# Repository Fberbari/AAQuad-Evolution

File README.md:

# AAQuad-Evolution
---

The AAQuad-Evolution is a flight computer I've designed to control a quadcopter. The computer takes care of continued stabilization in flight while leaving the pilot free to command roll, pitch, and yaw angles as well as altitude. The project is made up of a custom PCB, all the bare-metal C code that runs on the Atmega328pb processor and Matlab simulations used to design and tune the PID algorithms. This is very much a bare bones flight computer that is in no way as feature rich as BetaFlight or any of the other famous FOS flight controllers. Its advantage lies in its simplicity. Anyone with some understanding of the dynamics of flight, calculus, and circuitry could begin to understand the project without being faced with a mountain of complexity and no idea where to start. In the end, the AAQuad-Evolution continues to satisfy my curiosity for flight and increase my understanding of embedded systems all the while providing me with a creative outlet to try out all kinds of cool things.

## Flying the Quad
---

The commands are as such:

* Increasing/decreasing the throttle stick corresponds to an increase/decrease in the target altitude.
* Increasing/decreasing the rudder stick corresponds to an increase/decrease in the target azimuth (relative to the starting azimuth).
* Increasing/decreasing the aileron stick corresponds to an increase/decrease in the target bank angle.
* Increasing/decreasing the elevator stick corresponds to an increase/decrease in the target pitch angle.

The ranges for all the mentioned targets are defined in src/Pid.h.

## Calibrating the Quad
---

1. Before plugging in the battery, turn the transmitter on and put the throttle stick to full power.
2. Plug in the battery.
	* A solid green led will turn on, indicating calibration mode has been successfully entered.
3. Position the Quad on a level surface and make sure it is completely still.
4. Put the throttle stick to 0.
	* The led will turn off, indicating calibration has begun.
5. Once the led turns on again, the Quad has been successfully calibrated and is ready to be flown.

### Some in flight images

### Some close ups

## What's going on ?
---

So you want to understand how the AAQuad flies ? Great! Here is a high level explanation of what's going on.

Everything starts in main.c, which you'll find in the root directory of the project. If you go through that file, you'll find it's incredibly simple in principle. Here, we begin with a short delay to ensure all electrical systems have stabilized after power up. Next, we execute a calibration and finally, we call the controller state machine inside an infinite loop (this is where the magic happens).

Now, let's head into the src directory. Apart from main.c, this is where all the the source and header files are stored. Take a look at the state machine in Controller.c (the switch case statement inside the Controller_DoYourThingAndFlyTheQuadITrustYou function). The switch statement is organized in the order that the states get executed. Here's what's going on:

1. GetPilotInstructions: We check to see whether there are any new instructions from the receiver. If you take a look inside the PilotInstructions module, you'll see that the pwm signals sent from the ESC are read asynchronously via external and pin change interrupts. Those instructions get translated into percentages for commanded roll, pitch, yaw and altitude. If they are ready when PilotInstructions_ComputePilotResult is called, we pick them up. Otherwise, we just move on and pick them up the next time.

2. GetImuData: We collect the accelerometer, gyroscope and magnetometer data from the inertial measurement unit. This is also an interrupt based exchanged so when we call Imu_GetResult, we are just checking if the data is ready and picking it up if it is.

3. GetAltitude: We collect data from the ultrasonic distance sensor. Once again, it is an interrupt based exchange, so we are just checking and picking data up if it is ready.

4. TriggerNewMeasurements: Now that we've collected all the data of interest, we need to instruct the sensors to collect more data for us. This way, when the time comes once again to ask for it, it will be ready. For the IMU, this triggers an interrupt based SPI exchange that reads the registers that contain the relevant data. For the ultrasonic distance sensor, this sends the digital pulse instructing it to collect a new measurement.

5. FuseMeasurements: While the sensors do their thing, we begin to crunch the math. In this state, we fuse gyroscope and accelerometer data together using a Mahony filter. This filter returns the estimated orientation of the quad encoded in a quaternion.

6. ConvertToEuler: Since quaternions are very non linear and thus hard to use in a linear controller, we convert them into Euler angles. These are the familiar roll, pitch and yaw angles. At the same time, we also compute the derivatives of the Euler angles (representative of the angular velocity of the quad in every axis). This is for future use in the controller. It is done this way because computing a derivative from the change in measured angular positions leaves us very susceptible to noise. Since we have a gyroscope and measure the derivatives directly, we can use those values and avoid this problem.

7. ComputePid: Now that we know what the pilot wants and what the quad is doing, we can compute what we need the motors to do to achieve the pilot's intentions. This is done via multiple PID (proportional, integral, derivative) algorithms. This module also takes care of figuring out the takeoff sequence of the quad. What we get from it is an array of 4 floats that correspond to percentages of full power that need to be delivered to each motor to achieve the desired intentions.

8. SendToPwm: Once we know what we want the motors to do, we need to communicate that to them. To do so, we begin an interrupt based I2C exchange with a chip responsible for sending out PWM to the ESC.

9. WaitForTimer: Last, to keep things synchronous, we sit in this state until a timer says some set time has passed. Once that is the case, we go back to the GetPilotInstructions state and the cycle begins anew.

10. Failed: This state should never be reached in normal flight but exists in case a catastrophic failure needs to be handled. In the case that something goes horribly wrong in one of the modules (for example communication gets cut with one of our chips), we go to this state and the PWM output to the ESC gets immediately shutdown, causing the motors to stop spinning.

## Building it for yourself
---

A word of caution. This project was not designed to be reproduced, so it is fairly difficult to do so. That being said, if anyone does want to construct the PCB and tune then upload the software, here is what they would need to do:

### Prereq Hardware

* [Avr-Ice Jtag programmer](https://www.digikey.ca/en/product-highlight/a/atmel/atmel-ice-programmer-debugger?utm_adgroup=&utm_source=google&utm_medium=cpc&utm_campaign=Dynamic%20Search_EN_RLSA&utm_term=&productid=&gclid=Cj0KCQjw-r71BRDuARIsAB7i_QPVjor9MwRzLKq1k-X_j-4Pasl5VIqnCOX7berqcM59qXUvdlT64RQaAkUuEALw_wcB)
* A 4 channel ESC with 5V BEC that can handle 200 Hz PWM refresh rates
* A minimum 4 channel receiver that communicates over PWM
* Your favorite quadcopter frame, motors, and battery
* A transmitter capable of communicating with your esc of choice

### Prereq Software

* Atmel studio 7+
* Kicad 5+ (Optional, as the gerbers are already in the repo)
* Simulink 2019+, equipped with the aerospace blockset

### Building the PCB

Full gerber files and a BOM are present in the PCB/KicadFiles directory.
The only sensor not present in the BOM is the [ultrasonic distance sensor](https://www.sparkfun.com/products/15569).
You will also need to purchase the appropriate wires to connect the ESC, receiver, and ultrasonic sensor to the PCB.

### Adjusting the PID gains

If you know the mass, inertia tensor, and relationship between throttle percentage, force and torque of your quadcopter, you can adjust the appropriate blocks in the Simulink model and tune the PID gains. You can insert those gains into src/Pid.c.

### Compiling and uploading the software

Once the pcb is built, power it by connecting the ESC to the battery and plug in the Jtag programmer to the appropriate pins. To open the project in Atmel studio, open the project file present in /build. Then, click the compile button and the run button.

## License

This project is under the MIT license.

## Acknowledgements

* SOH Madgwick, whose implementation of the Mahony filter is used in this project.
* A shoutout to Anny Wang, who said: "Hey, wouldn't it be cool to build a quadcopter ?" back in 2018, which is how this project began :p.

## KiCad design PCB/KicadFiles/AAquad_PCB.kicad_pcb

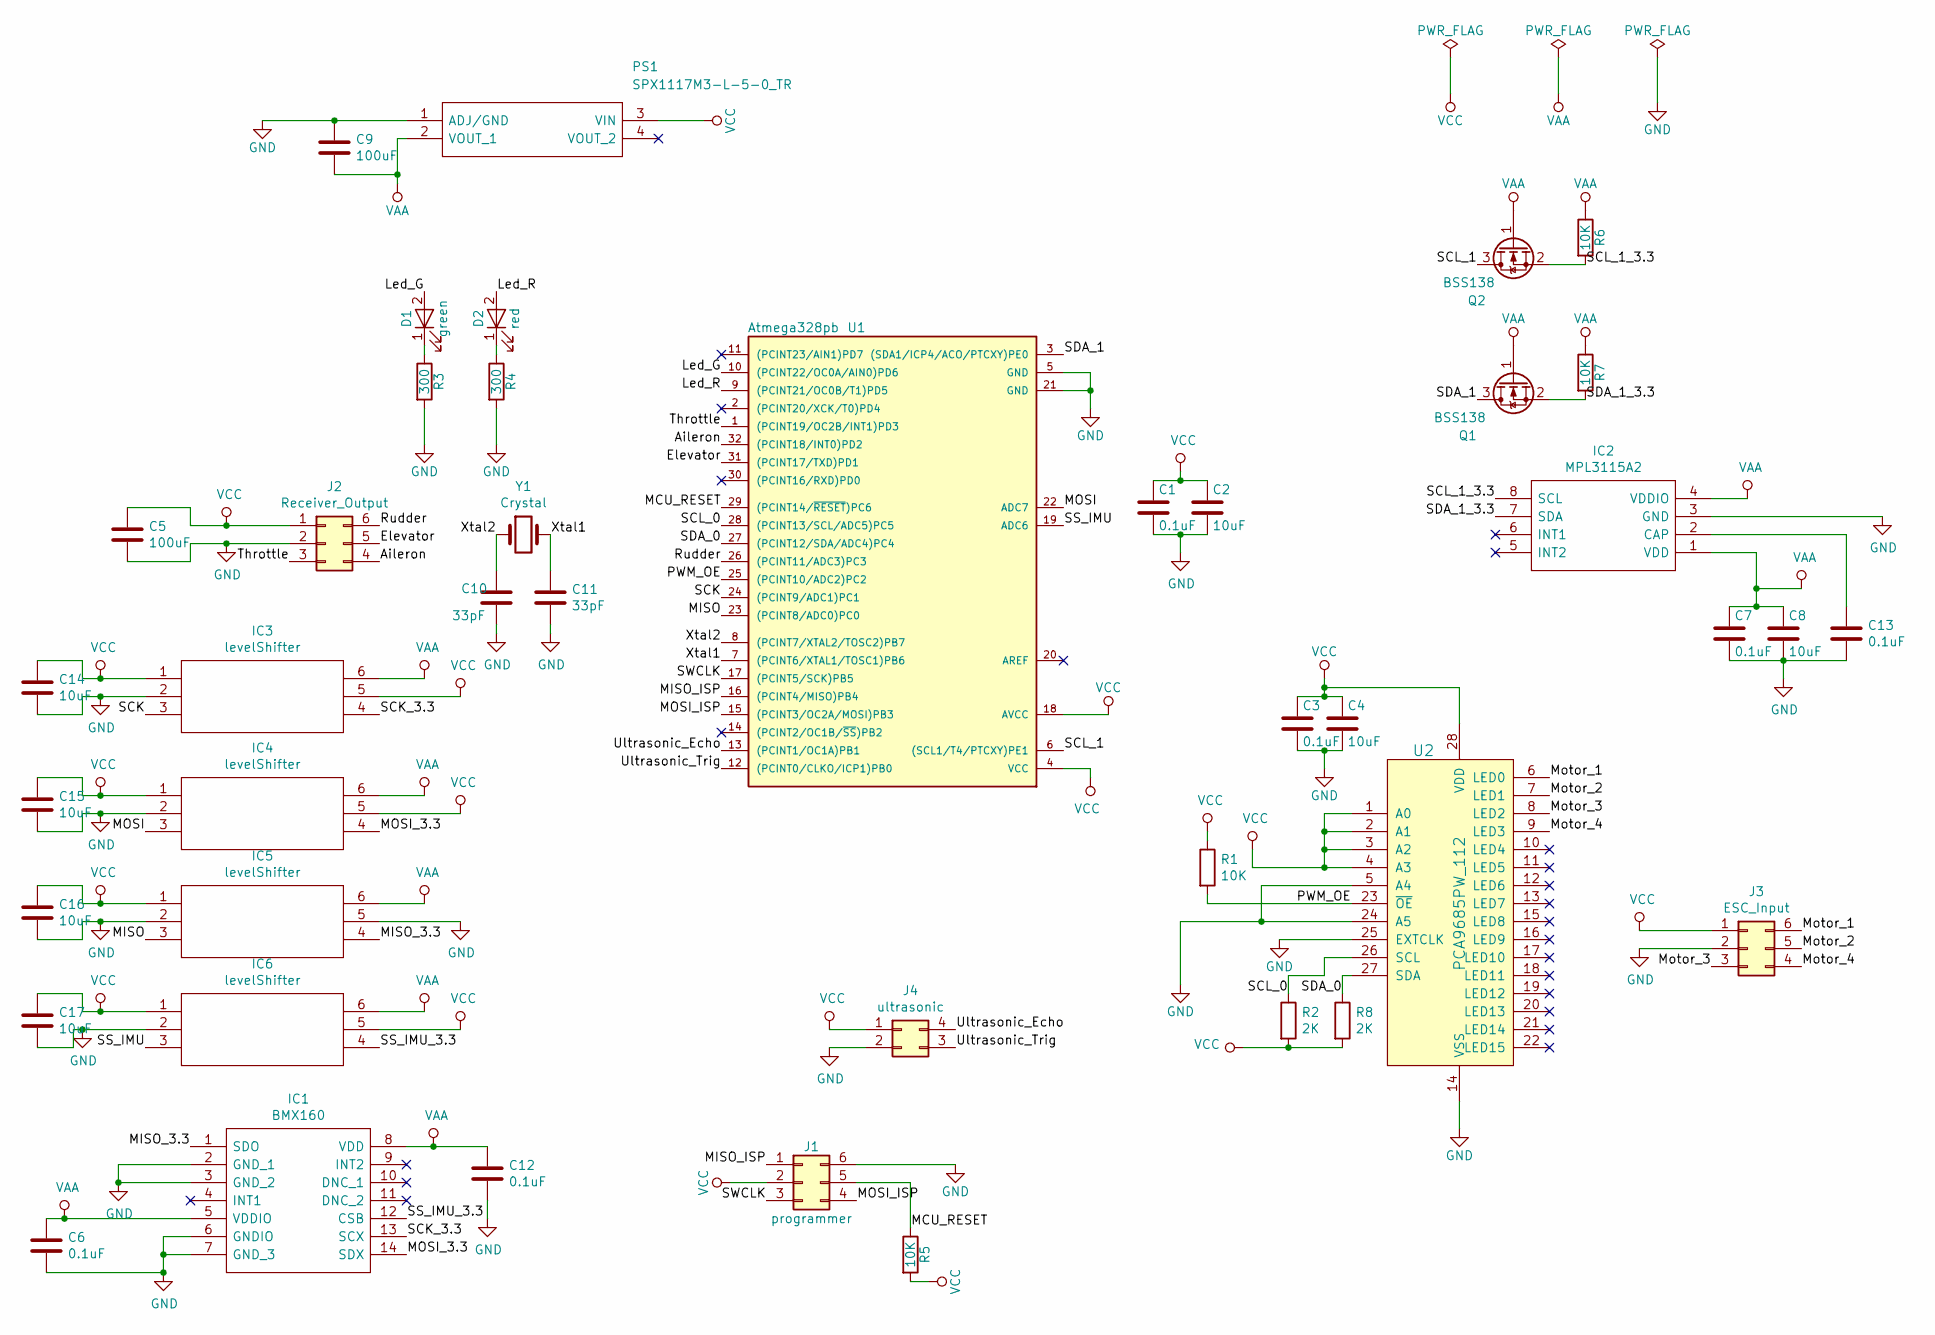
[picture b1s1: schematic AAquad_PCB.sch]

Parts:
C1, C3, C6, C7, C12, C13: 0.1uF; C_0805
C2, C4, C8: 10uF; C_0805
C5, C9: 100uF; C_1206_3216Metric
C10, C11: 33pF; C_0402_1005Metric
C14, C15, C16, C17: 10uF; C_0805_2012Metric
D1: green; LED_0805_HandSoldering
D2: red; LED_0805_HandSoldering
IC1: BMX160; bmx160; Manufacturer_Part_Number BMX160; Mouser Part Number 262-BMX160
IC2: MPL3115A2; Manufacturer_Part_Number MPL3115A2
IC3, IC4, IC5, IC6: levelShifter; 74LVC1T45GW_125; Mouser Part Number 771-74LVC1T45GW125
J1: programmer; PinHeader_2x03_P2.54mm_Vertical
J2: Receiver_Output; PinHeader_2x03_P2.54mm_Vertical
J3: ESC_Input; PinHeader_2x03_P2.54mm_Vertical
J4: ultrasonic; PinHeader_2x02_P2.54mm_Vertical
PS1: SPX1117M3-L-5-0_TR; SOT230P700X170-4N; Manufacturer_Part_Number SPX1117M3-L-5-0/TR
Q1, Q2: BSS138; SOT-23
R1, R5, R6, R7: 10K; R_0805_2012Metric
R2, R8: 2K; R_0805_2012Metric
R3, R4: 300; R_0805_2012Metric
U1: Atmega328pb; ATMEGA328PB-ANR
U2: PCA9685PW_112; TSSOP-28_W4.40mm; MPN PCA9685PW,112; Digi-Key_PN 568-8366-5-ND
Y1: Crystal; Crystal_SMD_7050-2pin_7.0x5.0mm

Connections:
/Aileron: J2.4, U1.32 ((PCINT18/INT0)PD2)
/Elevator: J2.5, U1.31 ((PCINT17/TXD)PD1)
/Led_G: D1.2 (A), U1.10 ((PCINT22/OC0A/AIN0)PD6)
/Led_R: D2.2 (A), U1.9 ((PCINT21/OC0B/T1)PD5)
/MCU_RESET: J1.5, R5.1, U1.29 ((PCINT14/~RESET~)PC6)
/MISO: IC5.3, U1.23 ((PCINT8/ADC0)PC0)
/MISO_3.3: IC1.1 (SDO), IC5.4
/MISO_ISP: J1.1, U1.16 ((PCINT4/MISO)PB4)
/MOSI: IC4.3, U1.22 (ADC7)
/MOSI_3.3: IC1.14 (SDX), IC4.4
/MOSI_ISP: J1.4, U1.15 ((PCINT3/OC2A/MOSI)PB3)
/Motor_1: J3.6, U2.6 (LED0)
/Motor_2: J3.5, U2.7 (LED1)
/Motor_3: J3.3, U2.8 (LED2)
/Motor_4: J3.4, U2.9 (LED3)
/PWM_OE: R1.2, U1.25 ((PCINT10/ADC2)PC2), U2.23 (~OE)
/Rudder: J2.6, U1.26 ((PCINT11/ADC3)PC3)
/SCK: IC3.3, U1.24 ((PCINT9/ADC1)PC1)
/SCK_3.3: IC1.13 (SCX), IC3.4
/SCL_0: R2.1, U1.28 ((PCINT13/SCL/ADC5)PC5), U2.26 (SCL)
/SCL_1: Q2.3 (D), U1.6 ((SCL1/T4/PTCXY)PE1)
/SCL_1_3.3: IC2.8 (SCL), Q2.2 (S), R6.2
/SDA_0: R8.1, U1.27 ((PCINT12/SDA/ADC4)PC4), U2.27 (SDA)
/SDA_1: Q1.3 (D), U1.3 ((SDA1/ICP4/ACO/PTCXY)PE0)
/SDA_1_3.3: IC2.7 (SDA), Q1.2 (S), R7.2
/SS_IMU: IC6.3, U1.19 (ADC6)
/SS_IMU_3.3: IC1.12 (CSB), IC6.4
/SWCLK: J1.3, U1.17 ((PCINT5/SCK)PB5)
/Throttle: J2.3, U1.1 ((PCINT19/OC2B/INT1)PD3)
/Ultrasonic_Echo: J4.4, U1.13 ((PCINT1/OC1A)PB1)
/Ultrasonic_Trig: J4.3, U1.12 ((PCINT0/CLKO/ICP1)PB0)
/Xtal1: C11.1, U1.7 ((PCINT6/XTAL1/TOSC1)PB6), Y1.2
/Xtal2: C10.1, U1.8 ((PCINT7/XTAL2/TOSC2)PB7), Y1.1
GND: C1.2, C2.2, C3.2, C4.2, C5.2, C6.1, C7.2, C8.2, C9.1, C10.2, C11.2, C12.1, C13.2, C14.2, C15.2, C16.2, C17.2, IC1.2 (GND_1), IC1.3 (GND_2), IC1.6 (GNDIO), IC1.7 (GND_3), IC2.3 (GND), IC3.2, IC4.2, IC5.2, IC5.5, IC6.2, J1.6, J2.2, J3.2, J4.2, PS1.1 (ADJ/GND), R3.2, R4.2, U1.5 (GND), U1.21 (GND), U2.5 (A4), U2.14 (VSS), U2.24 (A5), U2.25 (EXTCLK)
unnamed: C13.1, IC2.2 (CAP)
unnamed: D1.1 (K), R3.1
unnamed: D2.1 (K), R4.1
VAA: C6.2, C7.1, C8.1, C9.2, C12.2, IC1.5 (VDDIO), IC1.8 (VDD), IC2.1 (VDD), IC2.4 (VDDIO), IC3.6, IC4.6, IC5.6, IC6.6, PS1.2 (VOUT_1), Q1.1 (G), Q2.1 (G), R6.1, R7.1
VCC: C1.1, C2.1, C3.1, C4.1, C5.1, C14.1, C15.1, C16.1, C17.1, IC3.1, IC3.5, IC4.1, IC4.5, IC5.1, IC6.1, IC6.5, J1.2, J2.1, J3.1, J4.1, PS1.3 (VIN), R1.1, R2.2, R5.2, R8.2, U1.4 (VCC), U1.18 (AVCC), U2.1 (A0), U2.2 (A1), U2.3 (A2), U2.4 (A3), U2.28 (VDD)

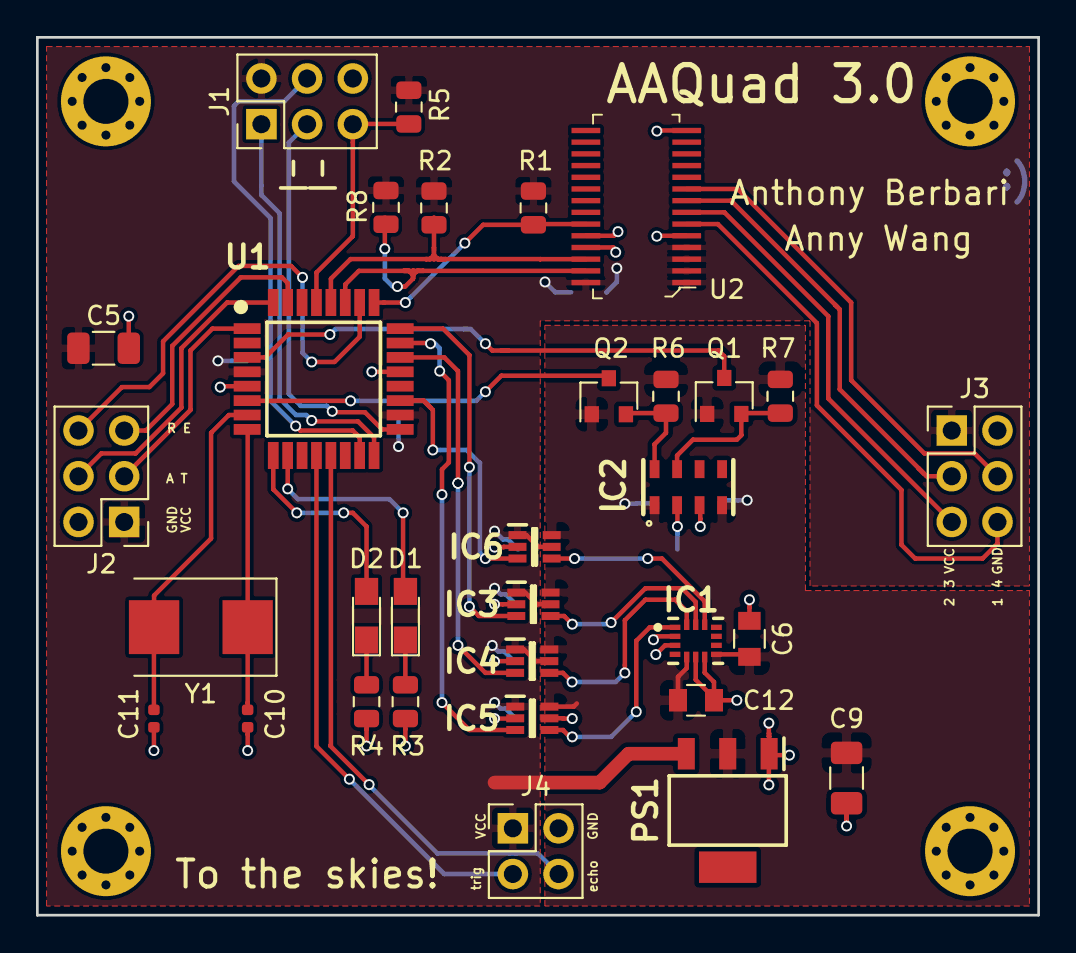
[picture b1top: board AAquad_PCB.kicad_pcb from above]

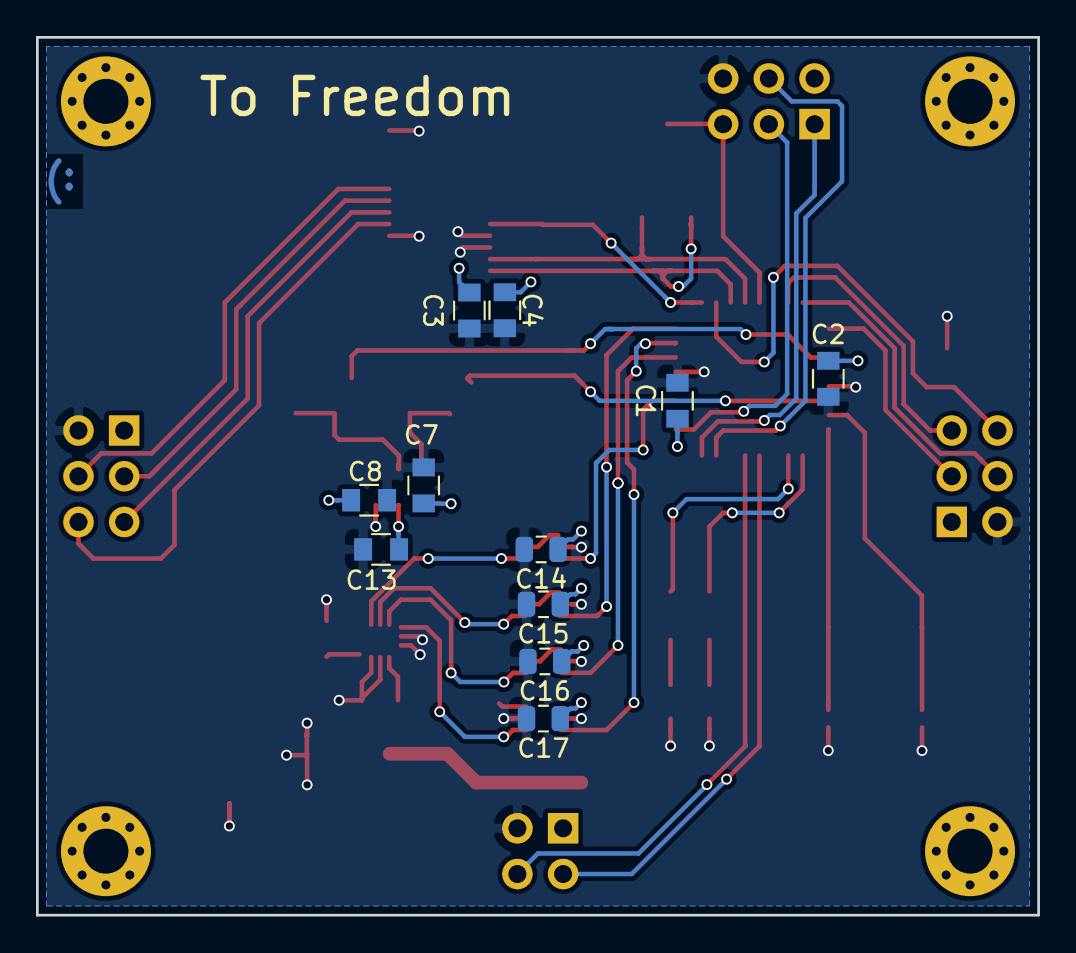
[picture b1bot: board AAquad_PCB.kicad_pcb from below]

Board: 2 copper layers, 55.6 x 48.8 mm, 43 parts (11 on the bottom side), 39 nets.

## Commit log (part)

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2019-03-02 created skeleton directories for the project
2019-03-03 Created the modules' header files
2019-03-03 Began developing the PilotInstructions Module
2019-03-09 Completed phase 1 --All 4 motors smoothly controlled in unison via flight computer
2019-03-10 Developped and unit tested the PilotInstructions module to the point where all receiver channels can be captured
2019-03-10 phase 2 of developement complete --all 4 receiver channels incorporated allowing control of 3 degrees of freedom and throttle
2019-03-18 Working on integrating accelerometer and gyroscope
2019-03-20 implemented the beginnings of a Complementary filter
2019-03-20 Added a periodic Sensor Reset and Complementary filter bug fixes
2019-03-25 Completed a physical Analysis of the AAQuad and used the results to build a tesing framework that was used to tune the PID
2019-04-13 Fixing tesyt runners for Pid ad Low pass filter to correspond to observed results
2019-04-21 ready for full test
2019-05-01 critical damping achieved, digital lowpass filter no longer necessary, gyro settings altered to filterin hardware
2019-05-02 added PID for the yaw axis and tuned the calibration module as well as the PID coefficients in accordance with a 3D test
2019-05-07 Tested and working on the actual aircraft.
2019-05-08 added KiCad and schematic files
2019-05-15 forced motors to 0 at startup
2019-05-15 added a readme
2019-05-19 adjusted SensorData and PilotInstructions API's to support saving and loading calibrations
2019-05-20 Working Calibration
2019-05-20 Moved a macro useful to Calibration into common.h and fixed README typos
2019-05-21 enabled accelerometer Calibration
2019-05-27 reduced the value that the computer associates to idle motors
2019-08-24 Completed PCB redesign
2019-08-24 Finished PCB Review. Sent out gerbers for manufacturing
2019-12-29 Updated Kicad Files and layout PDFs
2020-01-01 Checked in IDE project files
2020-01-04 Created the driver for the new IMU chip.
    Wrote and successfully tested an interrupt based SPI driver for the
    bmx160. The driver initialises the chip and allows collection of the
    accelerometer, gyroscope and magnetometer data.
    On top of this, the processor clock has been sped up to 20MHz and the
    spi clock runs at 10 MHz.
    Although the driver has been tested, it is not yet integrated with the
2020-01-12 Made the pwmchip I2C driver interrupt based
    There are now no blocking calls associated with the pwm chip. The I2C
    driver runs at 100 KHz.
    Although the driver has been tested and functions, it is not yet
    integrated with the rest of the code. With this commit, the code will
    still compile, but will not fly a quadcopter properly until changes are
    made to the controller module.
2020-01-18 Developed a driver for the ultrasonic distance sensor
    The flight computer can now use altitude data from the ultrasonic
    distance sensor via the Altitude module. No calls to this module are
    polling based.
2020-01-21 Updated README to reflect the current state of the project
2020-01-21 Renamed "Schematics" directory to "PCB" and added some pictures of the newest PCB.
2020-02-02 Removed the obsolete SensorData module
    Now that the drivers for the IMU and altitude sensor have been completed
    and tested, it is fine to delete the SensorData module, which was
    responsible for reading various sensors on the previous iteration of
    the PCB. Not only were the sensors different, making it useless, but
    the SensorData module relied on polling, making the decision to
    deprecate it more reasonable than a decision to update it.
2020-02-02 Flipped boolean "isFallingEdge" flag with logical not instead of XOR
    It is safer to use logical operations rather than bitwise ones on
    boolean values.
2020-04-22 Centralized the interrupt functionality relevant to the Pilot instructions module inside it.
    Previous to this change, the external interrupts responsible for reading
    the pwm signals coming from the receiver were initialized in main and
    the ISRs existed in "interrupts.c". With this change, The
    PilotInstructions module takes care of initializing its interrupts and
    holds the ISRs, thus removing the need for an interrupt module and
    cleaning up main.
2020-04-25 Imu_get_result now returns gyro data in rad/s
    Previous to this, gyro units were arbitrary. Magnetometer and
    accelerometer data remain in arbitrary units, as those vectors are
    normalized. This is reflected in the function's description.
2020-04-25 Changed documentation of PilotInstructions_ComputePilotResult to reflect that the return struct is only modified in the case of success.
2020-04-26 Integrated multiple modules into Controller to add functionality up to gathering and fusing all data from the sensors.
    This is a large and important commit. As of this commit, Controller's
    state machine reflects the design from the flowchart and can effectively
    collect Pilot instructions, altitude, and IMU data from the relevant
    hardware. This is all done in a real time loop (20ms period at the
    moment).
    The other new change is the introduction of the MahonyAHRS module, which
2020-04-26 Fixed typo in Controller_Init documentation.
2020-04-28 Inserted all appropriate mechanical specifications in the matlab model
    With this commit, the simulink model uses the quad's actual mass, moment
    of inertia tensor, and motor forces/torques.
2020-04-28 Built a PID module that reflects the simulink model.
    This commit sees the PID module drastically change from what it was in
    the last version. It's addition also completes the main control loop,
    meaning it is now possible to begin physical testing of the quad.
    The PID module is essentially an exact replica of the matlab code that
    makes up the simulink controller.
2020-04-29 Fixed important bug in Altitude.c
    Previous to this change, the echo pulse of the ultrasonic distance
    sensor would only be properly measured if it represented an altitude
    below 50 cm and if the timer that measured it did not wrap around.
    With this change, the timer that measures the echo pulse has been
    prescaled by a factor of 64, so all altitudes in the sensor's range can
    be measured. Also, the edge case of the timer overflowing during the
2020-04-30 Rebuilt the calibration module
    Now, the pilot has the ability to request a calibration of the
    ultrasonic distance sensor and of his own controls. That calibration
    gets stored in eeprom and is used to adjust the modules every time the
    board is powered on.
    The other thing done by calibration, on each power cycle, is ensure that
    the pilot's command of 0 yaw corresponds to the direction the Quad is
2020-04-30 Increased control loop frequency from 50 to 200 Hz
    Doing some testing, it was observed that it takes roughly 3 ms for all
    the math to be done in a single control loop iteration. Since the Imu
    supports 200 Hz gyro and acc data rates, it is certainly possible to
    output results at this speed.
    Although it was not extensively tested, increasing the control loop
    frequency can only be beneficial, as finer corrections can be made more
2020-04-30 Fixed typo in a macro used to config the IMU
    The macro ACC_ODR_800_OSR4 was used to config the gyro rather than the
    correct GYRO_ODR_800_OSR4. They both happened to evaluate to the same
    value, so this change will not affect actual performance in any way.
2020-05-01 Updated simulink model to simulate the new 200 Hz Control loop.
    As a result, new Pid gains were also found.
2020-05-03 Reduced the value associated with MOTOR_VALUE_NO_SPIN
    The old value was slightly too high, so the motors sometimes refused to start (there is a safety mechanism in the esc that does not allow the motors to start spinning unless a state of near 0 throttl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
2020-05-03 Completed the calibration sequence of the magnetometer and gyroscope
    As of this commit, there is a sequence of commands (that will be explained in the readme) that the pilot can use on startup to calibrate the magnetometer and gyroscope. The magnetometer calibration h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
    Aside from the above changes, the Calibration module now, once again, leverages the Leds to indicate to the pilot what stage of Cal
2020-05-03 Removed 2 #includes that were already in the Common module.
2020-05-04 Updated the Pid module with the latest gains and covered yaw edge case
    A few commits ago, the control loop was sped up to 200 Hz. As a result, the matlab model was updated and the optimal gains changed. Those latest gains are now reflected in the Pid module.
    Furthermore, it was discovered that there are possible discontinuities in the way the Pid algorithms treated the z axis. For example, if the pilot commanded -170 degrees while the quad was at 175 deg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
2020-05-04 Added led sequence that triggers once the Quad is ready to fly.
2020-05-04 Updated Readme and added some pictures
2020-05-05 Calibration now also calibrates the accelerometer
    With this change, the entire IMU can be calibrated by the Calibration
    module.
    To facilitate this change, I decided to have the Imu module report
    accelerometer data in mg (1g being earth's acceleration) rather than in
    arbitrary units.
2020-05-09 Added safety functionality to disable the output in case of failure.
    With this commit, if the controller state machine ends up in the failed
    state for any reason, the PwmChip is instructed to turn off all its
    outputs, which in turn means the motors stop spinning.
    The solution is immune to a communication failure with the PwmChip
    aswell.
2020-08-10 Used the ZYX euler angles rather than the original XYZ
    Through some experimentation, it was discovered that if there was a non
    negligible amount of yaw, roll and pitch would become coupled with the
    XYZ sequence. This problem is not present in the ZYX sequence. In that
    case the coupling would be between yaw and pitch when roll was large.
    However, that is not an issue because unlike yaw, which can routinely
    take on practically any angular value, the roll and pitch angles will
2020-08-10 Used non magnetometer API of Mahony rather than full version
    I discovered that I live so far north that the earth's magnetic field around here is not actually perpendicular to gravity. This really confused the Mahony algorithm. In the future, I will make some 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
2020-08-11 Added initialisation delays
    There was a bug plaging this project for many weeks. It was eventually
    understood to be caused by a failure to properly initialize the
    accelerometer, which seems to be a result of not giving the SPI module
    enough time to initialise before putting it in use. This problem was
    solved by adding a delay to allow that time. A delay was also added to
    the very first line of the main function, for good measure.
2020-08-11 Adjusted Matlab model to account for new Euler sequence
    The simulink model now reflects that I am using the ZYX sequence instead of the
    XYZ one. The pid gains were calculated again and Pid.c was updated accordingly.
2020-08-23 final commit before release
    The big change in this commit is the addition of a lowPass filter to
    smooth altitude data as it was found to contain outliers that threw off
    the derivative wildly.
    The other major change is a further optimization of the pid gains. The
    new gains were found by the matlab model to give better results.
    All other changes are typos that were fixed and comments that were
2020-08-23 Went to the MIT license rather than GPL 3
    The choice to use gpl was made too hastily when this project was started. Deciding to use the MIT license means more people could potentially use the AAQuad-Evolution IP however they would like.
2020-09-01 Updated Readme with some an in flight gif and some pictures
2020-09-10 Added safety functionality to detect transmitter failure
